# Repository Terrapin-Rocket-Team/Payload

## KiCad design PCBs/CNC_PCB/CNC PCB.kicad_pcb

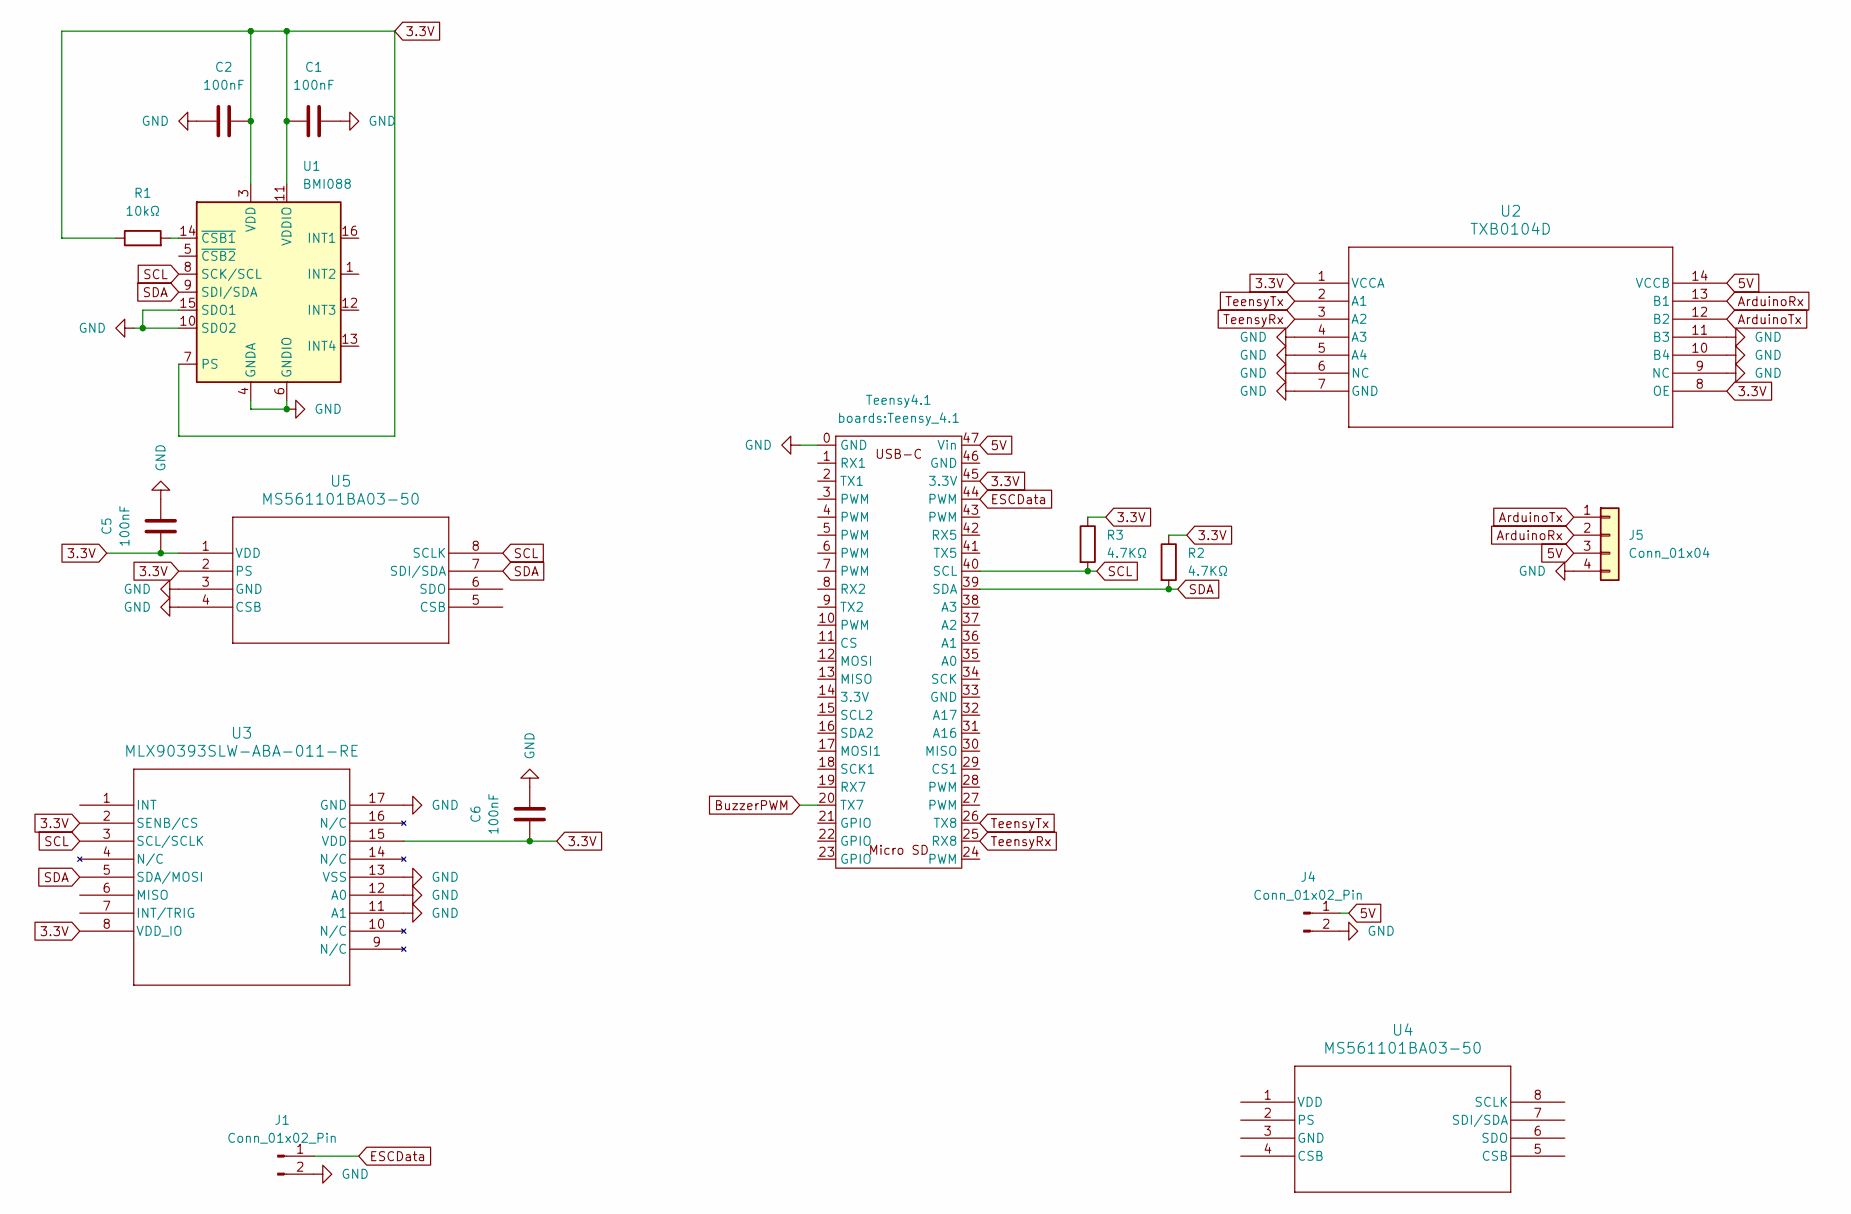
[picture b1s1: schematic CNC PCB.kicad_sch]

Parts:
C1, C2, C5, C6: 100nF; C_0603_1608Metric
J1, J4: Conn_01x02_Pin; JST_XH_B2B-XH-A_1x02_P2.50mm_Vertical
J5: Conn_01x04; JST_XH_B4B-XH-AM_1x04_P2.50mm_Vertical
R1: 10kΩ; R_0603_1608Metric
R2, R3: 4.7KΩ; R_0603_1608Metric
Teensy4.1: Teensy_4.1
U1: BMI088; Bosch_LGA-16_4.5x3mm_P0.5mm_LayoutBorder7x1y_ClockwisePinNu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
U2: TXB0104D; D14
U3: MLX90393SLW-ABA-011-RE; QFN-16_MLX90393_MEL
U4, U5: MS561101BA03-50; SON8_MS5611_TEC

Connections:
3.3V: C1.2, C2.1, C5.2, C6.2, R1.1, R2.1, R3.1, Teensy4.1.45 (3.3V), U1.3 (VDD), U1.7 (PS), U1.11 (VDDIO), U2.1 (VCCA), U2.8 (OE), U3.2 (SENB/CS), U3.8 (VDD_IO), U3.15 (VDD), U5.1 (VDD), U5.2 (PS)
5V: J4.1, J5.3, Teensy4.1.47 (Vin), U2.14 (VCCB)
ArduinoRx: J5.2, U2.13 (B1)
ArduinoTx: J5.1, U2.12 (B2)
BuzzerPWM: Teensy4.1.20 (TX7)
ESCData: J1.1, Teensy4.1.44 (PWM)
GND: C1.1, C2.2, C5.1, C6.1, J1.2, J4.2, J5.4, Teensy4.1.0 (GND), U1.2 (GNDA), U1.4 (GNDA), U1.6 (GNDIO), U1.10 (SDO2), U1.15 (SDO1), U2.4 (A3), U2.5 (A4), U2.6 (NC), U2.7 (GND), U2.9 (NC), U2.10 (B4), U2.11 (B3), U3.11 (A1), U3.12 (A0), U3.13 (VSS), U3.17 (GND), U5.3 (GND), U5.4 (CSB)
unnamed: R1.2, U1.14 (~CSB1)
SCL: R3.2, Teensy4.1.40 (SCL), U1.8 (SCK/SCL), U3.3 (SCL/SCLK), U5.8 (SCLK)
SDA: R2.2, Teensy4.1.39 (SDA), U1.9 (SDI/SDA), U3.5 (SDA/MOSI), U5.7 (SDI/SDA)
TeensyRx: Teensy4.1.25 (RX8), U2.3 (A2)
TeensyTx: Teensy4.1.26 (TX8), U2.2 (A1)

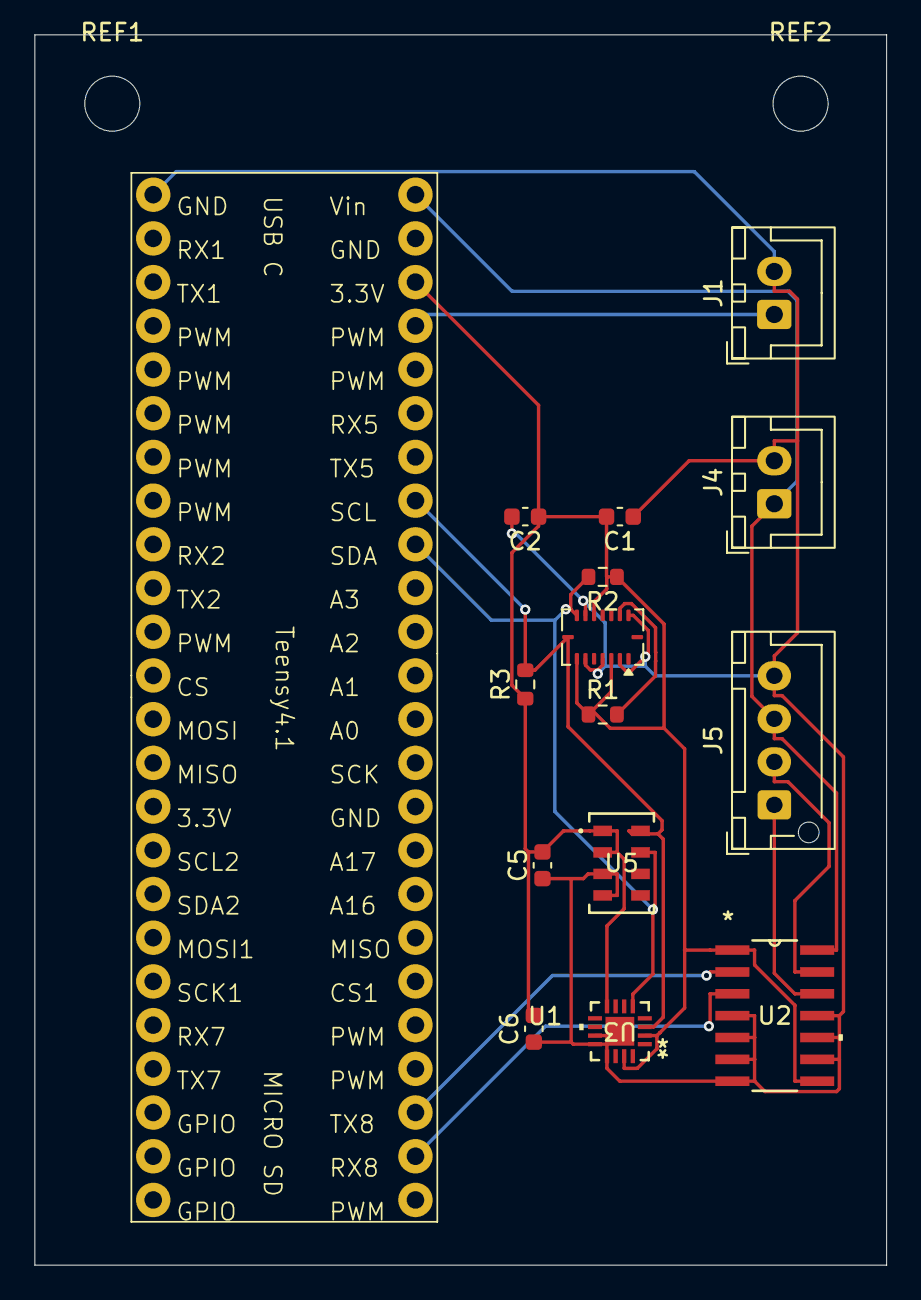
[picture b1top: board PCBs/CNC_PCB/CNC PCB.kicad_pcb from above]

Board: 2 copper layers, 49.5 x 71.5 mm, 17 parts (0 on the bottom side), 11 nets.

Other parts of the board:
REF1, REF2: MountingHole_3.2mm_M3

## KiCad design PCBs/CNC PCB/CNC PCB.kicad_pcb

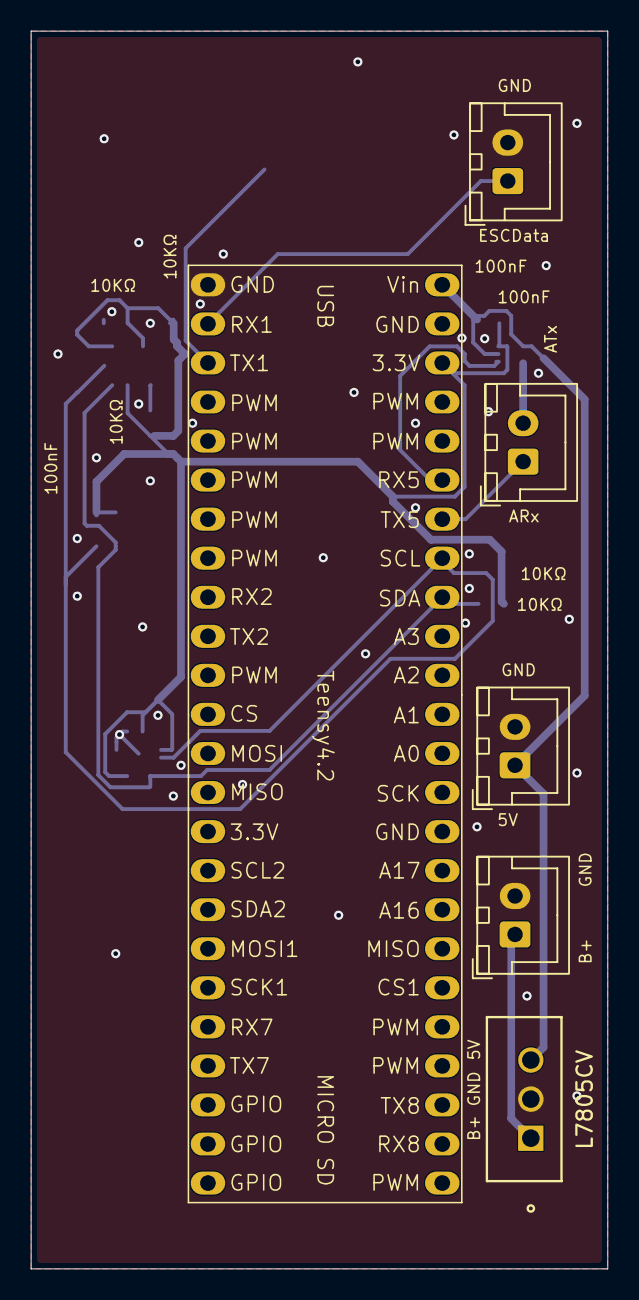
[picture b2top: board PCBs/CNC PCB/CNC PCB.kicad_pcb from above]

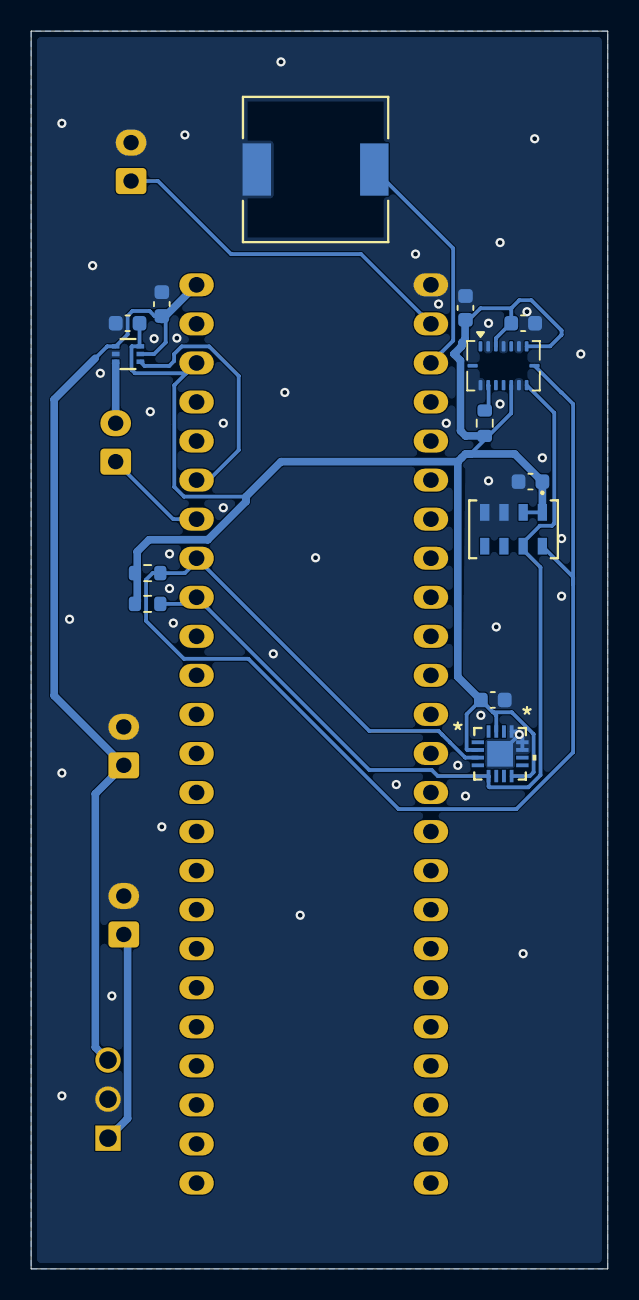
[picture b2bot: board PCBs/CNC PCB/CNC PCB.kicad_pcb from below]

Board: 2 copper layers, 37.5 x 80.5 mm, 20 parts (14 on the bottom side), 12 nets.

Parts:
BZ1: Buzzer; PKMCS0909E4000-R1_MUR
C1, C2, C3, C4, C5, C6: 100nF; C_0603_1608Metric
J1, J2, J3, J4: Conn_01x02_Pin; JST_XH_B2B-XH-A_1x02_P2.50mm_Vertical
R1: 10kΩ; R_0603_1608Metric
R2, R3: 10KΩ; R_0603_1608Metric
Teensy4.2: Teensy_4.1_Compact
U1: BMI088; Bosch_LGA-16_4.5x3mm_P0.5mm_LayoutBorder7x1y_ClockwisePinNu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
U2: SN74LVC; SOT-563_DIO
U3: MLX9039; QFN-16_MLX90393_MEL
U4: L7805CV
U5: MS5607; SON8_MS5611_TEC

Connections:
3.3V: C1.2, C2.1, C4.2, C5.2, C6.2, R1.1, R2.1, R3.1, Teensy4.2.3V1 (3.3V), U1.3 (VDD), U1.7 (PS), U1.11 (VDDIO), U2.6 (VCCB), U3.2 (SENB/CS), U3.8 (VDD_IO), U3.15 (VDD), U5.1 (VDD), U5.2 (PS)
5V: C3.2, J4.1, Teensy4.2.5V (VIN), U2.1 (VCCA), U2.5 (DIR), U4.3 (OUTPUT)
ArduinoTx: J2.2, U2.3 (A)
B+: J3.1, U4.1 (INPUT)
BuzzerPWM: BZ1.1 (+), Teensy4.2.1 (TX1)
ESCData: J1.1, Teensy4.2.0 (RX1)
GND: BZ1.2 (-), C1.1, C2.2, C3.1, C4.1, C5.1, C6.1, J1.2, J3.2, J4.2, Teensy4.2.G (GND), U1.2 (GNDA), U1.4 (GNDA), U1.6 (GNDIO), U1.10 (SDO2), U1.15 (SDO1), U2.2 (GND), U3.11 (A1), U3.12 (A0), U3.13 (VSS), U3.17 (GND), U4.2 (GROUND), U5.3 (GND), U5.4 (CSB)
unnamed: R1.2, U1.14 (~CSB1)
SCL: R3.2, Teensy4.2.19 (SCL), U1.8 (SCK/SCL), U3.3 (SCL/SCLK), U5.8 (SCLK)
SDA: R2.2, Teensy4.2.18 (SDA), U1.9 (SDI/SDA), U3.5 (SDA/MOSI), U5.7 (SDI/SDA)
TeensyRx: Teensy4.2.21 (RX5), U2.4 (B)
TeensyTx: J2.1, Teensy4.2.20 (TX5)

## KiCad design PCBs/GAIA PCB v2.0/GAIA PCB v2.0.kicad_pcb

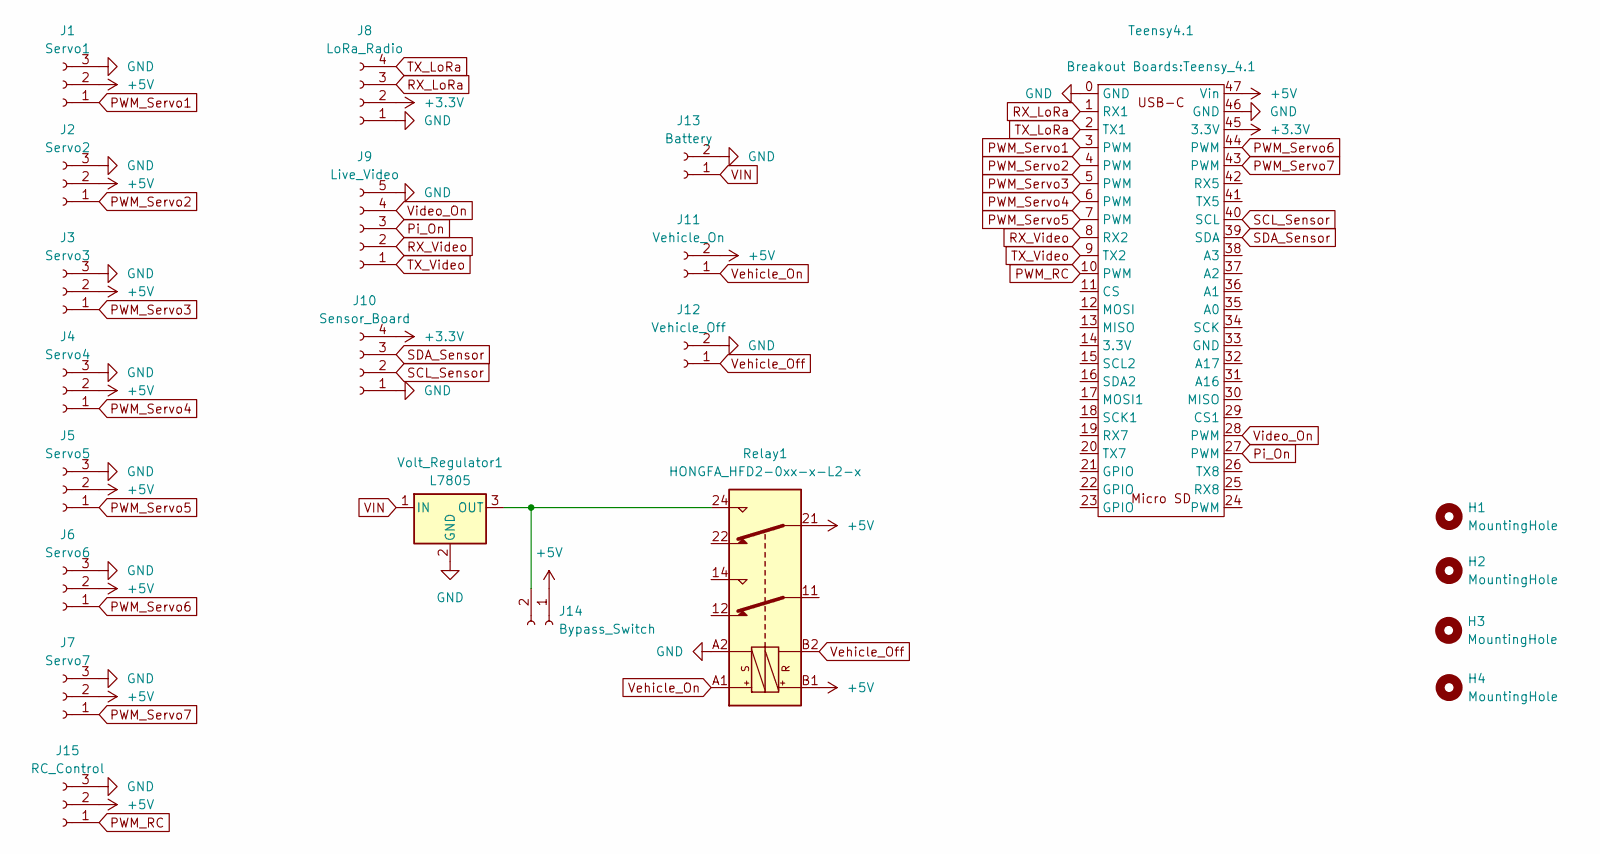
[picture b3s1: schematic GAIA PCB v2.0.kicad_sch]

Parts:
H1, H2, H3, H4: MountingHole; MountingHole_3.2mm_M3
J1: Servo1; JST_XH_B3B-XH-A_1x03_P2.50mm_Vertical
J2: Servo2; JST_XH_B3B-XH-A_1x03_P2.50mm_Vertical
J3: Servo3; JST_XH_B3B-XH-A_1x03_P2.50mm_Vertical
J4: Servo4; JST_XH_B3B-XH-A_1x03_P2.50mm_Vertical
J5: Servo5; JST_XH_B3B-XH-A_1x03_P2.50mm_Vertical
J6: Servo6; JST_XH_B3B-XH-A_1x03_P2.50mm_Vertical
J7: Servo7; JST_XH_B3B-XH-A_1x03_P2.50mm_Vertical
J8: LoRa_Radio; JST_XH_B4B-XH-A_1x04_P2.50mm_Vertical
J9: Live_Video; JST_XH_B5B-XH-A_1x05_P2.50mm_Vertical
J10: Sensor_Board; JST_XH_B4B-XH-A_1x04_P2.50mm_Vertical
J11: Vehicle_On; JST_XH_B3B-XH-A_1x03_P2.50mm_Vertical
J12: Vehicle_Off; JST_XH_B3B-XH-A_1x03_P2.50mm_Vertical
J13: Battery; JST_XH_B2B-XH-A_1x02_P2.50mm_Vertical
J14: Bypass_Switch; JST_XH_B2B-XH-A_1x02_P2.50mm_Vertical
J15: RC_Control; JST_XH_B3B-XH-A_1x03_P2.50mm_Vertical
Relay1: HONGFA_HFD2-0xx-x-L2-x; Relay_DPDT_Omron_G6AK
Teensy4.1: Teensy_4.1
Volt_Regulator1: L7805; TO-220-3_Vertical

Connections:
+3.3V: J8.2, J10.4, Teensy4.1.45 (3.3V)
+5V: J1.2, J2.2, J3.2, J4.2, J5.2, J6.2, J7.2, J11.2, J14.1, J15.2, Relay1.21, Relay1.B1, Teensy4.1.47 (Vin)
GND: J1.3, J2.3, J3.3, J4.3, J5.3, J6.3, J7.3, J8.1, J9.5, J10.1, J12.2, J13.2, J15.3, Relay1.A2, Teensy4.1.0 (GND), Teensy4.1.46 (GND), Volt_Regulator1.2 (GND)
unnamed: J14.2, Relay1.24, Volt_Regulator1.3 (OUT)
PWM_RC: J15.1, Teensy4.1.10 (PWM)
PWM_Servo1: J1.1, Teensy4.1.3 (PWM)
PWM_Servo2: J2.1, Teensy4.1.4 (PWM)
PWM_Servo3: J3.1, Teensy4.1.5 (PWM)
PWM_Servo4: J4.1, Teensy4.1.6 (PWM)
PWM_Servo5: J5.1, Teensy4.1.7 (PWM)
PWM_Servo6: J6.1, Teensy4.1.44 (PWM)
PWM_Servo7: J7.1, Teensy4.1.43 (PWM)
Pi_On: J9.3, Teensy4.1.27 (PWM)
RX_LoRa: J8.3, Teensy4.1.1 (RX1)
RX_Video: J9.2, Teensy4.1.8 (RX2)
SCL_Sensor: J10.2, Teensy4.1.40 (SCL)
SDA_Sensor: J10.3, Teensy4.1.39 (SDA)
TX_LoRa: J8.4, Teensy4.1.2 (TX1)
TX_Video: J9.1, Teensy4.1.9 (TX2)
VIN: J13.1, Volt_Regulator1.1 (IN)
Vehicle_Off: J12.1, Relay1.B2
Vehicle_On: J11.1, Relay1.A1
Video_On: J9.4, Teensy4.1.28 (PWM)

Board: 2 copper layers, 22 parts (0 on the bottom side), 23 nets, no tracks yet.

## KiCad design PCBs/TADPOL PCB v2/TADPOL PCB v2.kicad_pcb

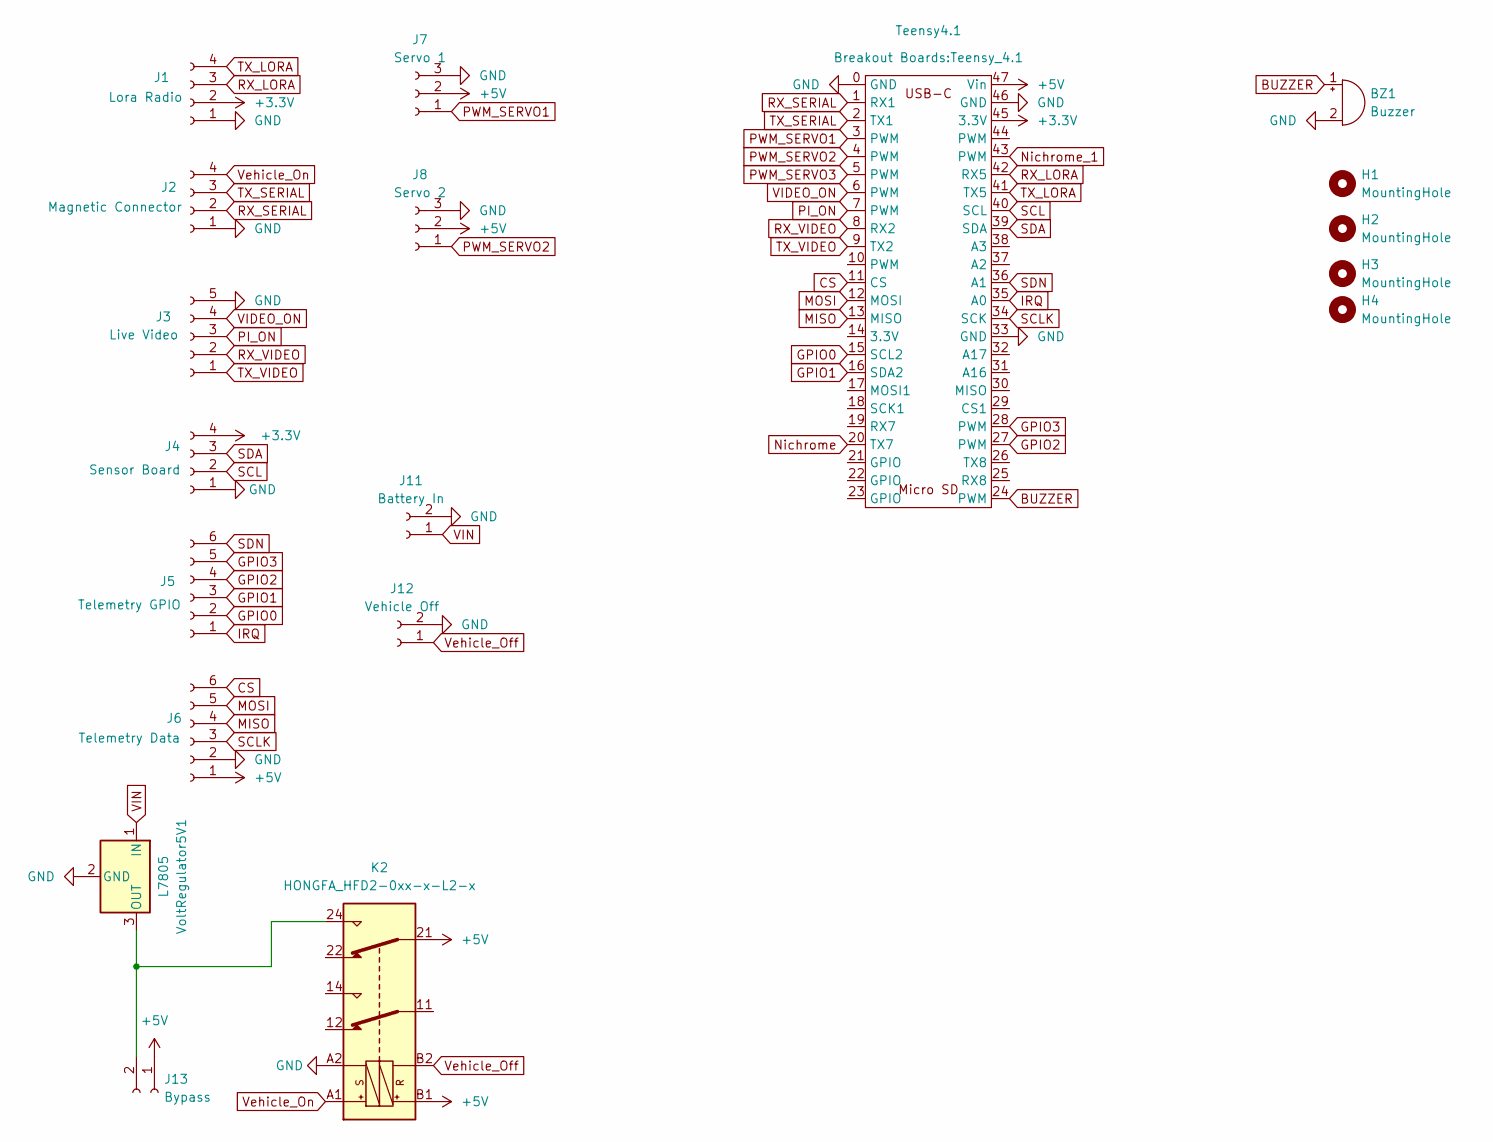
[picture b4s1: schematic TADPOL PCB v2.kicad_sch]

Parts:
BZ1: Buzzer; Buzzer_12x9.5RM7.6
H1, H2, H3, H4: MountingHole; MountingHole_3.2mm_M3
J1: Lora Radio; JST_XH_B4B-XH-A_1x04_P2.50mm_Vertical
J2: Magnetic Connector; JST_XH_B4B-XH-A_1x04_P2.50mm_Vertical
J3: Live Video; JST_XH_B5B-XH-A_1x05_P2.50mm_Vertical
J4: Sensor Board; JST_XH_B4B-XH-A_1x04_P2.50mm_Vertical
J5: Telemetry GPIO; JST_XH_B6B-XH-A_1x06_P2.50mm_Vertical
J6: Telemetry Data; JST_XH_B6B-XH-A_1x06_P2.50mm_Vertical
J7: Servo 1; JST_XH_B3B-XH-A_1x03_P2.50mm_Vertical
J8: Servo 2; JST_XH_B3B-XH-A_1x03_P2.50mm_Vertical
J11: Battery In; JST_XH_B2B-XH-A_1x02_P2.50mm_Vertical
J12: Vehicle Off; JST_XH_B2B-XH-A_1x02_P2.50mm_Vertical
J13: Bypass; JST_XH_B2B-XH-A_1x02_P2.50mm_Vertical
K2: HONGFA_HFD2-0xx-x-L2-x; Relay_DPDT_Omron_G6AK
Teensy4.1: Teensy_4.1
VoltRegulator5V1: L7805; TO-220-3_Vertical

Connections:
+3.3V: J1.2, J4.4, Teensy4.1.45 (3.3V)
+5V: J6.1, J7.2, J8.2, J13.1, K2.21, K2.B1, Teensy4.1.47 (Vin)
BUZZER: BZ1.1 (+), Teensy4.1.24 (PWM)
CS: J6.6, Teensy4.1.11 (CS)
GND: BZ1.2 (-), J1.1, J2.1, J3.5, J4.1, J6.2, J7.3, J8.3, J11.2, J12.2, K2.A2, Teensy4.1.0 (GND), Teensy4.1.33 (GND), Teensy4.1.46 (GND), VoltRegulator5V1.2 (GND)
GPIO0: J5.2, Teensy4.1.15 (SCL2)
GPIO1: J5.3, Teensy4.1.16 (SDA2)
GPIO2: J5.4, Teensy4.1.27 (PWM)
GPIO3: J5.5, Teensy4.1.28 (PWM)
IRQ: J5.1, Teensy4.1.35 (A0)
MISO: J6.4, Teensy4.1.13 (MISO)
MOSI: J6.5, Teensy4.1.12 (MOSI)
unnamed: J13.2, K2.24, VoltRegulator5V1.3 (OUT)
Nichrome: Teensy4.1.20 (TX7)
Nichrome_1: Teensy4.1.43 (PWM)
PI_ON: J3.3, Teensy4.1.7 (PWM)
PWM_SERVO1: J7.1, Teensy4.1.3 (PWM)
PWM_SERVO2: J8.1, Teensy4.1.4 (PWM)
PWM_SERVO3: Teensy4.1.5 (PWM)
RX_LORA: J1.3, Teensy4.1.42 (RX5)
RX_SERIAL: J2.2, Teensy4.1.1 (RX1)
RX_VIDEO: J3.2, Teensy4.1.8 (RX2)
SCL: J4.2, Teensy4.1.40 (SCL)
SCLK: J6.3, Teensy4.1.34 (SCK)
SDA: J4.3, Teensy4.1.39 (SDA)
SDN: J5.6, Teensy4.1.36 (A1)
TX_LORA: J1.4, Teensy4.1.41 (TX5)
TX_SERIAL: J2.3, Teensy4.1.2 (TX1)
TX_VIDEO: J3.1, Teensy4.1.9 (TX2)
VIDEO_ON: J3.4, Teensy4.1.6 (PWM)
VIN: J11.1, VoltRegulator5V1.1 (IN)
Vehicle_Off: J12.1, K2.B2
Vehicle_On: J2.4, K2.A1

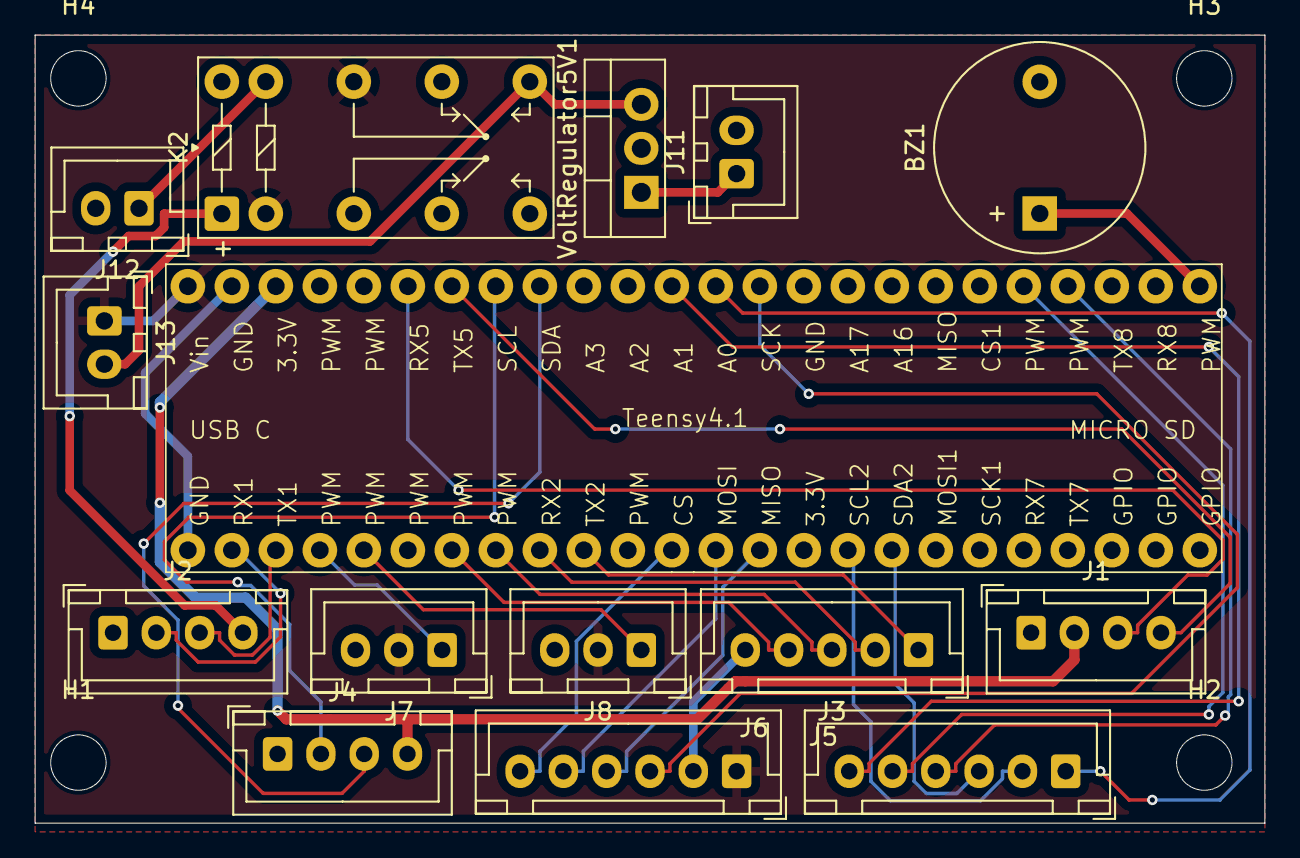
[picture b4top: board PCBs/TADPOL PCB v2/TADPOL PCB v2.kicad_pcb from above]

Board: 2 copper layers, 71.0 x 45.5 mm, 19 parts (0 on the bottom side), 30 nets.

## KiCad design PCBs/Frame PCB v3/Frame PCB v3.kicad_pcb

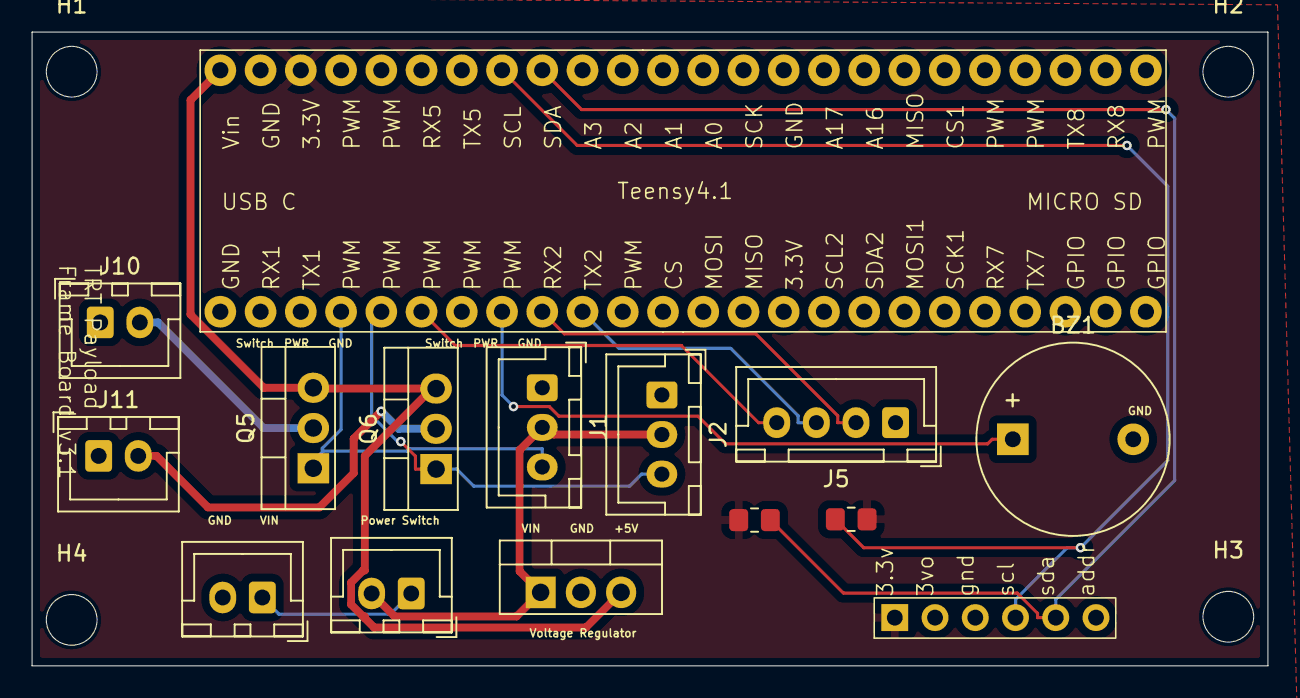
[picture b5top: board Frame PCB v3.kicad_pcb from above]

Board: 2 copper layers, 78.0 x 40.0 mm, 19 parts (0 on the bottom side), 15 nets.

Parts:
BH1: BH1750
BZ1: Buzzer; Buzzer_12x9.5RM7.6
H1, H2, H3, H4: MountingHole; MountingHole_3.2mm_M3
J1: Nichrome 1; JST_XH_B3B-XH-A_1x03_P2.50mm_Vertical
J2: Nichrome 2; JST_XH_B3B-XH-A_1x03_P2.50mm_Vertical
J3: Battery in; JST_XH_B2B-XH-A_1x02_P2.50mm_Vertical
J5: BayConnector; JST_XH_B4B-XH-A_1x04_P2.50mm_Vertical
J6: Switch; JST_XH_B2B-XH-A_1x02_P2.50mm_Vertical
J10, J11: Nichrome; JST_XH_B2B-XH-A_1x02_P2.50mm_Vertical
Q5, Q6: Nichrome; TO-220-3_Vertical
R1, R2: 3.3kΩ; R_0805_2012Metric_Pad1.20x1.40mm_HandSolder
Teensy4.1: Teensy_4.1
q1: Voltage regulator; TO-220-3_Vertical

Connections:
+3.3V: BH1.0 (VIN), R1.1, R2.2, Teensy4.1.45 (3.3V)
+5V: Q5.3 (S), Q6.3 (S), Teensy4.1.47 (Vin), q1.3 (E)
+9V: J1.2, J2.2, J6.2, q1.1 (B)
BuzzerPin: BZ1.1 (-), Teensy4.1.7 (PWM)
GND: BH1.2 (GND), BZ1.2 (+), J1.1, J2.1, J3.2, J5.1, J10.1, J11.1, Teensy4.1.0 (GND), q1.2 (C)
unnamed: J3.1, J6.1
unnamed: J10.2, Q5.2 (D)
unnamed: J11.2, Q6.2 (D)
Nichrome1: J1.3, Q5.1 (G), Teensy4.1.3 (PWM)
Nichrome2: J2.3, Q6.1 (G), Teensy4.1.4 (PWM)
SCL: BH1.3 (SCL), R2.1, Teensy4.1.40 (SCL)
SDA: BH1.4 (SDA), R1.2, Teensy4.1.39 (SDA)
VehicleOn: J5.4, Teensy4.1.5 (PWM)
VehicleRX: J5.3, Teensy4.1.9 (TX2)
VehicleTX: J5.2, Teensy4.1.8 (RX2)

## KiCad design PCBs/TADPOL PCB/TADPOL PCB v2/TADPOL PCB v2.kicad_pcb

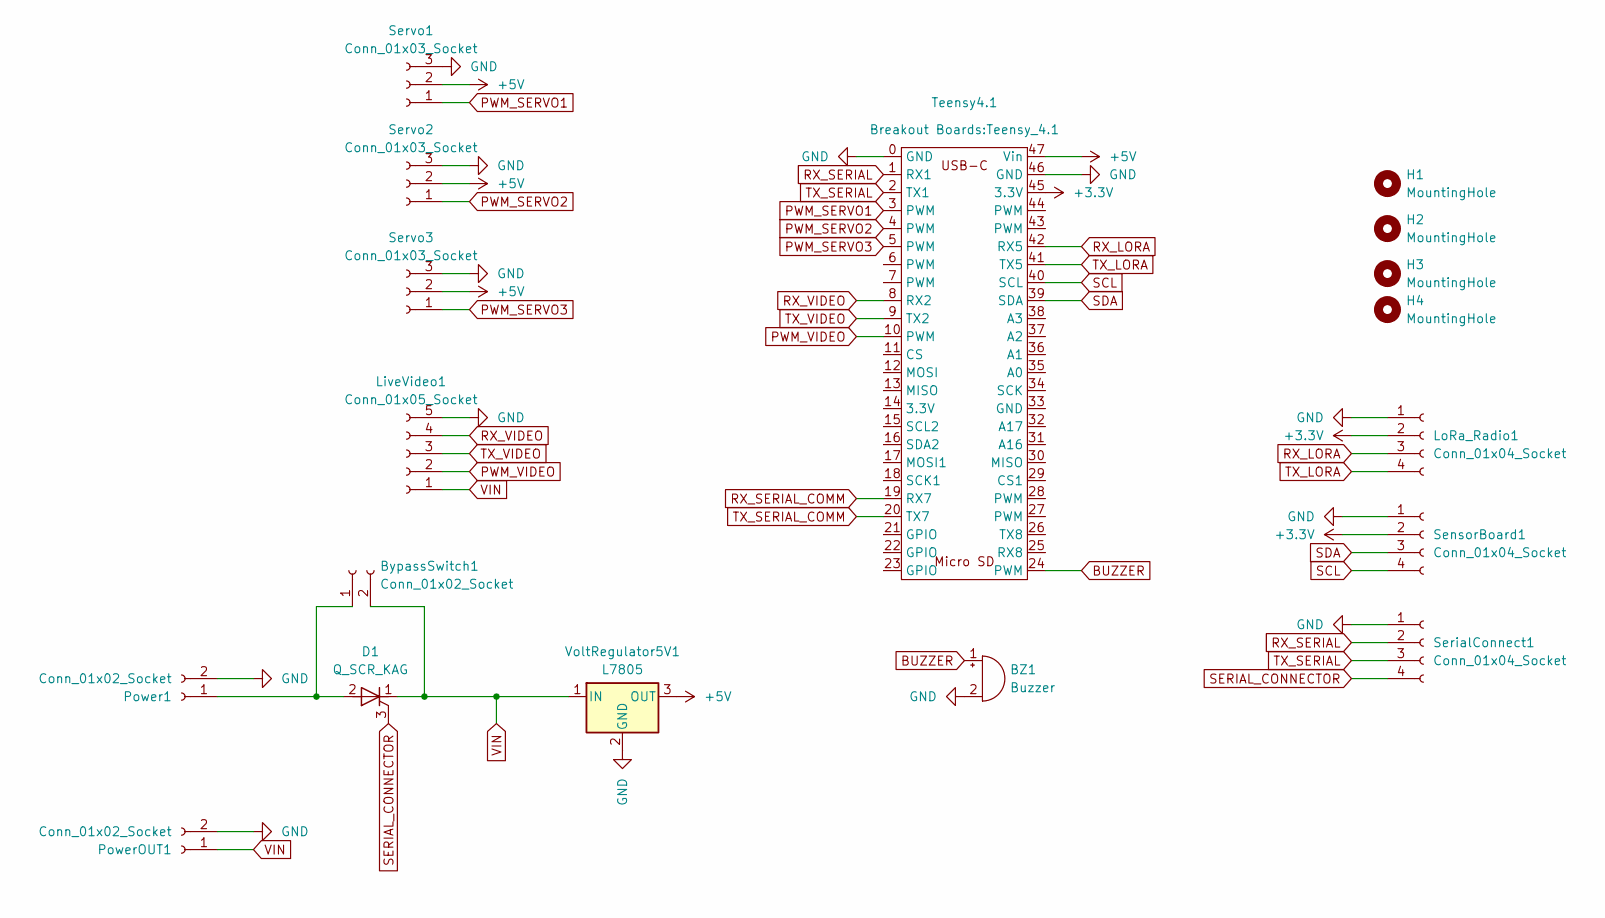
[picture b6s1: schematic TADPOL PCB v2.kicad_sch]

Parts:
BZ1: Buzzer; Buzzer_12x9.5RM7.6
BypassSwitch1: Conn_01x02_Socket; JST_XH_B2B-XH-A_1x02_P2.50mm_Vertical
D1: Q_SCR_KAG; TO-220-3_Vertical
H1, H2, H3, H4: MountingHole; MountingHole_3.2mm_M3
LiveVideo1: Conn_01x05_Socket; JST_XH_B5B-XH-A_1x05_P2.50mm_Vertical
LoRa_Radio1: Conn_01x04_Socket; JST_XH_B4B-XH-A_1x04_P2.50mm_Vertical
Power1: Conn_01x02_Socket; JST_XH_B2B-XH-A_1x02_P2.50mm_Vertical
PowerOUT1: Conn_01x02_Socket; JST_XH_B2B-XH-A_1x02_P2.50mm_Vertical
SensorBoard1: Conn_01x04_Socket; JST_XH_B4B-XH-A_1x04_P2.50mm_Vertical
SerialConnect1: Conn_01x04_Socket; JST_XH_B4B-XH-A_1x04_P2.50mm_Vertical
Servo1, Servo2, Servo3: Conn_01x03_Socket; JST_XH_B3B-XH-A_1x03_P2.50mm_Vertical
Teensy4.1: Teensy_4.1
VoltRegulator5V1: L7805; TO-220-3_Vertical

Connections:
+3.3V: LoRa_Radio1.2, SensorBoard1.2, Teensy4.1.45 (3.3V)
+5V: Servo1.2, Servo2.2, Servo3.2, Teensy4.1.47 (Vin), VoltRegulator5V1.3 (OUT)
BUZZER: BZ1.1 (+), Teensy4.1.24 (PWM)
GND: BZ1.2 (-), LiveVideo1.5, LoRa_Radio1.1, Power1.2, PowerOUT1.2, SensorBoard1.1, SerialConnect1.1, Servo1.3, Servo2.3, Servo3.3, Teensy4.1.0 (GND), Teensy4.1.46 (GND), VoltRegulator5V1.2 (GND)
unnamed: BypassSwitch1.1, D1.2 (A), Power1.1
PWM_SERVO1: Servo1.1, Teensy4.1.3 (PWM)
PWM_SERVO2: Servo2.1, Teensy4.1.4 (PWM)
PWM_SERVO3: Servo3.1, Teensy4.1.5 (PWM)
PWM_VIDEO: LiveVideo1.2, Teensy4.1.10 (PWM)
RX_LORA: LoRa_Radio1.3, Teensy4.1.42 (RX5)
RX_SERIAL: SerialConnect1.2, Teensy4.1.1 (RX1)
RX_SERIAL_COMM: Teensy4.1.19 (RX7)
RX_VIDEO: LiveVideo1.4, Teensy4.1.8 (RX2)
SCL: SensorBoard1.4, Teensy4.1.40 (SCL)
SDA: SensorBoard1.3, Teensy4.1.39 (SDA)
SERIAL_CONNECTOR: D1.3 (G), SerialConnect1.4
TX_LORA: LoRa_Radio1.4, Teensy4.1.41 (TX5)
TX_SERIAL: SerialConnect1.3, Teensy4.1.2 (TX1)
TX_SERIAL_COMM: Teensy4.1.20 (TX7)
TX_VIDEO: LiveVideo1.3, Teensy4.1.9 (TX2)
VIN: BypassSwitch1.2, D1.1 (K), LiveVideo1.1, PowerOUT1.1, VoltRegulator5V1.1 (IN)

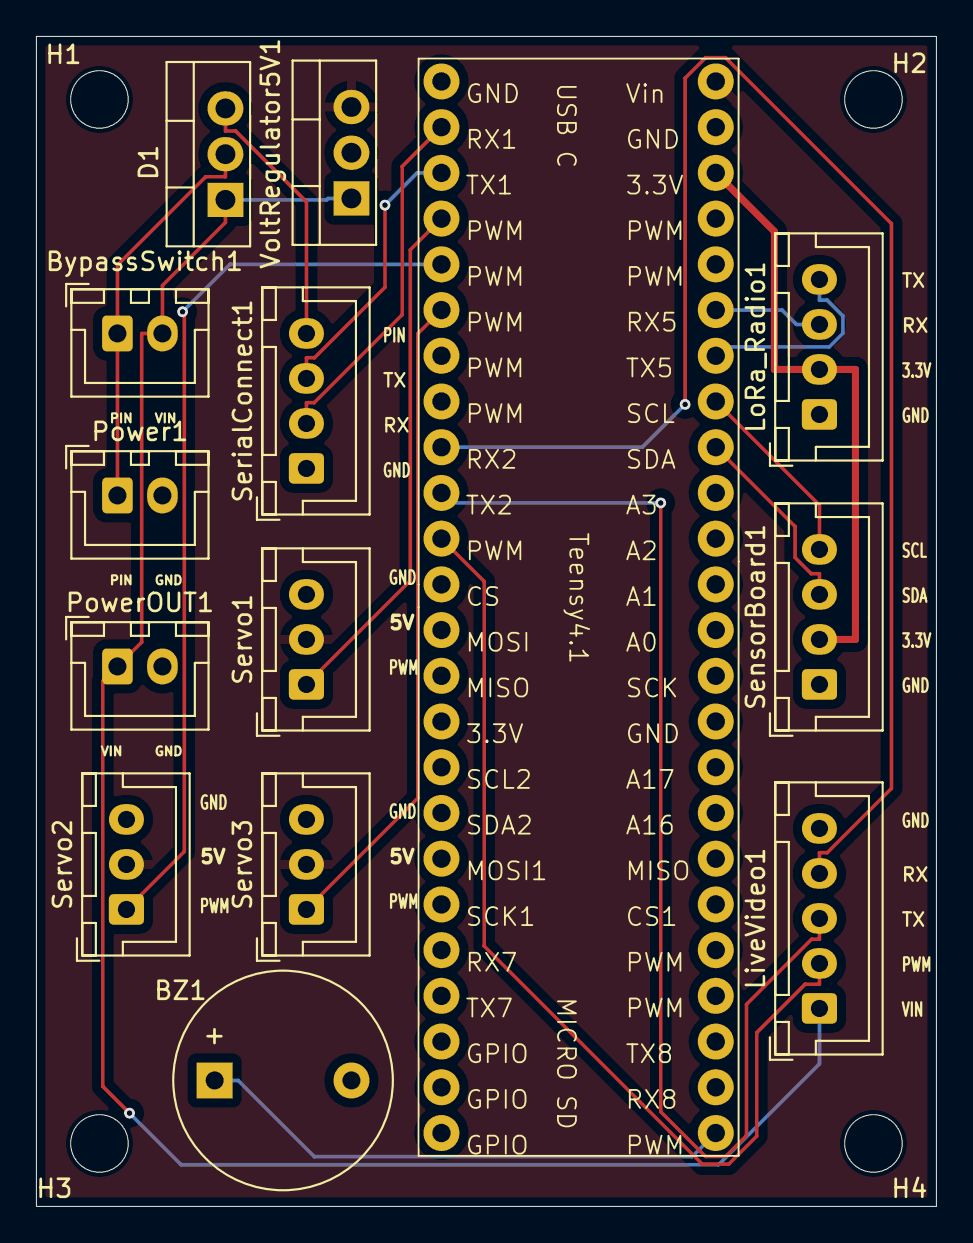
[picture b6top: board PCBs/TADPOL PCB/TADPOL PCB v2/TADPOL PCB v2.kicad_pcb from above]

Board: 2 copper layers, 50.0 x 65.0 mm, 18 parts (0 on the bottom side), 19 nets.

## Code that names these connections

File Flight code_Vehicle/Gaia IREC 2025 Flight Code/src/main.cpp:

#include <Arduino.h>
#include <Wire.h>
#include <vector>
#include <Servo.h>
#include "Si4463.h"
#include "422Mc80_4GFSK_009600H.h"
#include "MMFS.h"
#include "VehicleState.h"


mmfs::MAX_M10S gps;
mmfs::DPS368 baro;
mmfs::BMI088andLIS3MDL vehicle_imu;
Logger logger;

Sensor *sensors[] = {&gps, &baro, &vehicle_imu};

VehicleState vehicle(sensors, 3, nullptr);

MMFSConfig config = MMFSConfig()
                        .withState(&vehicle)
                        .withBuzzerPin(13)
                        .withBBPin(13)
                        .withUpdateRate(10)
                        .withBBAsync(true, 50);

MMFSSystem computer = MMFSSystem(&config);
int itterationloop = 0;

Servo actuator;

APRSConfig aprsConfigAvionics = {"KD3BBD", "ALL", "WIDE1-1", PositionWithoutTimestampWithoutAPRS, '\\', 'M'};
APRSConfig aprsConfigPayload = {"KQ4TCN", "ALL", "WIDE1-1", PositionWithoutTimestampWithoutAPRS, '\\', 'M'};
uint8_t encoding[] = {7, 4, 4};
APRSTelem avionicsTelem(aprsConfigAvionics);
Message msgAvionics;
Message msgPayload;

const char *avionicsCall = "KD3BBD";
const char *airbrakeCall = "KC3UTM";
Si4463HardwareConfig hwcfg = {
    MOD_4GFSK,        // modulation
    DR_4_8k,          // data rate
    (uint32_t)430e6,  // frequency (Hz)
    POWER_COTS_30dBm, // tx power (127 = ~20dBm)
    48,               // preamble length
    16,               // required received valid preamble
};

Si4463PinConfig pincfg = {
    &SPI, // spi bus to use
    10,   // cs
    15,   // sdn
    14,   // irq
    24,   // gpio0
    25,   // gpio1
    36,   // gpio2
    37,   // gpio3
};

Si4463 radio(hwcfg, pincfg);
void setup()
{
  computer.init();
  getLogger().recordLogData(mmfs::INFO_, "Entering Setup");  
  actuator.attach(2);
  if (radio.begin(CONFIG_422Mc80_4GFSK_009600H, sizeof(CONFIG_422Mc80_4GFSK_009600H)))
    {
        bb.onoff(BUZZER, 1000);
        getLogger().recordLogData(ERROR_, "Radio initialized.");
    }
    else
    {
        bb.onoff(BUZZER, 200, 3);
        getLogger().recordLogData(INFO_, "Radio failed to initialize.");
    }
  getLogger().recordLogData(mmfs::INFO_, "Leaving Setup");
}
uint32_t payloadTimer = millis();
uint32_t debugTimer = millis();
uint32_t txTimeout = millis();
bool sendPayload = false;
bool lookingForAvionics = true;

void loop() {
  if (computer.update()) {  
    if (vehicle.stage == GLIDING) {
      //This is ugly I know
      if (itterationloop < 40) {
        vehicle.servoOutput = 1350;
      }
      else if (itterationloop < 80) {
        vehicle.servoOutput = 1550;
      }
      else if (itterationloop < 120) {
        vehicle.servoOutput = 1750;
      }
      else if (itterationloop < 160) {
        vehicle.servoOutput = 1850;
      }
      else if (itterationloop < 260) {
        vehicle.servoOutput = 900;
      }
      else {
        itterationloop = 0;
      }
      itterationloop++;
      actuator.writeMicroseconds(vehicle.servoOutput);
    }
  }
   if (millis() - txTimeout > 200 && lookingForAvionics && radio.avail())
    {
        msgAvionics.size = radio.readRXBuf(msgAvionics.buf, Message::maxSize);
        char call[7] = {0};
        memset(call, 0, sizeof(char));
        memcpy(call, msgAvionics.buf, 6);
        Serial.println(call);
        if (strcmp(call, avionicsCall) == 0)
        {
            Serial.println("Got avionics telem");
            msgAvionics.decode(&avionicsTelem);
            payloadTimer = millis();
            lookingForAvionics = false;
            sendPayload = true;
        }
        radio.available = false;
    }

    if (millis() - payloadTimer > 500 && sendPayload)
    // if (millis() - payloadTimer > 1000)
    {
        // payloadTimer = millis();
        sendPayload = false;
        Serial.print("Timer after avionics is ");
        Serial.print(millis() - payloadTimer);
        Serial.println(", sending own telem");

        double orient[3] = {vehicle_imu.getAngularVelocity().x(), vehicle_imu.getAngularVelocity().y(), vehicle_imu.getAngularVelocity().z()};
        APRSTelem aprs = APRSTelem(aprsConfigPayload, gps.getPos().x(), gps.getPos().y(), baro.getAGLAltFt(), vehicle.getVelocity().z(), gps.getHeading(), orient, 0);

        aprs.stateFlags.setEncoding(encoding, 3);
        uint8_t arr[] = {(uint8_t)(int)baro.getTemp(), (uint8_t)vehicle.getStage(), (uint8_t)gps.getFixQual()};
        aprs.stateFlags.pack(arr);
        radio.send(aprs);

        txTimeout = millis();
        lookingForAvionics = true;
    }

    if (millis() - debugTimer > 500)
    {
        debugTimer = millis();
        Serial.println("here");
        Serial.println(radio.state);
        Serial.println(radio.readFRR(0));
    }

    radio.update();

}

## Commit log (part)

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2024-11-13 New python PID code
2024-11-20 serial connection code
2024-12-04 Updates to teensy code
2024-12-06 oct flight code
2024-12-06 compiled initial mule code with bmp and bno
2024-12-06 added light sensor
2024-12-06 created staging for the mule
2024-12-06 moved over power on and release functions from last year
2024-12-06 first cut servo vehicle flight code
2024-12-06 included the breakout for the gps
2024-12-06 got it to compile
2024-12-06 got rid of tail rotor stuff
2024-12-06 Added Nichrome test code
2024-12-06 fixed titling
2024-12-06 moved servo stuff over
2024-12-06 Updated launch code
2024-12-07 dec launch data
2024-12-07 Record extra state data
2024-12-07 flight code changes
2024-12-15 designed frame board v3
2024-12-15 vehicle board
2024-12-19 created frame v3 gerber
2024-12-22 Added Sled Test PD Controller
2024-12-28 added simulations of different estimations of vehicle speed
2025-01-02 updated code for next launch
2025-01-18 converted bench tests to brushless
2025-02-01 updated tail rotor mmfs to present
2025-02-01 untested flight code. moved over pd stuff from brushlessPDcontrol bench test
2025-02-01 added back nav stuff. just not using
2025-02-01 changed update rate
2025-02-02 Flight Code
2025-02-03 payload flight code that flew
2025-02-18 new PCB
2025-02-23 PCB v2
2025-02-23 Update fp-info-cache
2025-03-01 changed PID params
2025-03-07 fixed scr pcb
2025-03-09 Updated PCB
2025-03-10 created camera control code
2025-03-13 updated PCBS
2025-03-13 updated pcb hole spacing
2025-03-13 fixed traces
2025-03-23 added AbbasVehicleCode
2025-03-24 Added code for drop testing of the parafoil based on BrushlessPDControl code
2025-03-24 fixed data logging and errors
2025-03-26 added pd controller and servo control, fixed data logging
2025-03-26 fixing staging
2025-03-27 fixed staging
2025-03-27 bench test code
2025-03-27 working bench test code, servos move and imu detects angle
2025-03-27 added bench test logic to flight code
2025-03-27 added some comments
2025-03-29 cleaned up mmfs stuff
2025-03-29 updated timing to use mmfs timing
2025-03-29 vehicle just turns left
2025-04-18 fixed Gaia Board
2025-04-30 pushed new code for basic HIL stuff
2025-04-30 added correct code, previous push was outdated
2025-05-02 wrote out HITL code for comms
    -just did a really simple loop where x and y values increase to make sure comms work
    -integrate simulation code using past tail rotor simulation data
2025-05-03 hitl tweaks
2025-05-13 bench code for drogue chute
2025-05-20 added drogue chute code
2025-05-20 edits
2025-05-20 fixed compile error
2025-06-05 Changed PCB folder structure
2025-06-08 Preliminary flight code
2025-06-11 Final Flight Code
2025-08-07 new pcb prototype schematic
2025-09-15 pcb updates
2026-02-14 added cnc control from akshay
2026-02-14 cnc control can build
2026-02-18 can read sensor data now, using astraRocket
2026-02-20 added bench and serial test code
2026-02-23 working bench code in cnc-bench
2026-03-17 working cnc bench code
2026-03-17 updated flight code
2026-03-18 fixed data logging
2026-03-20 working flight code
2026-03-20 changes :D
2026-03-27 added FileLoader
2026-03-28 test
2026-03-28 Add FileLoader class and integrated gcode file reading into main - still need to test
2026-03-31 Modularized all cnc sequences into class
2026-04-18 Update bench test CNC code
2026-06-07 Fix Teensy CNC control file loading and launch sequencing
2026-06-07 Update CNC sequence and clear GRBL response buffer
2026-06-07 working g code cnc

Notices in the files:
parts and their libraries:
Copyright 2016 Accelerated Designs. All rights reserved.
